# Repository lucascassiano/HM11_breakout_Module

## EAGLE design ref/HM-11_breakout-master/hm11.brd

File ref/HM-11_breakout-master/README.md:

# REFERENCE: 
https://platis.solutions
I'm not the author, I just uploaded here to start making changes on this board file.

# HM-11 BLE module breakout board
Eagle PCB files for a HM-11 Bluetooth Low Energy module, breakout board. Based on the work by [Genoil](https://github.com/Genoil/smartwatch).

Order it directly from [OSH Park](https://oshpark.com/shared_projects/1uC5vV5p) (3.25$ for 3 boards).

Read the story behind it at my [blog](https://platis.solutions/blog/2015/06/11/breakout-board-hm-11-ble/), where you will also find other useful resources such as links to code for a sample Android application.

## Board renders

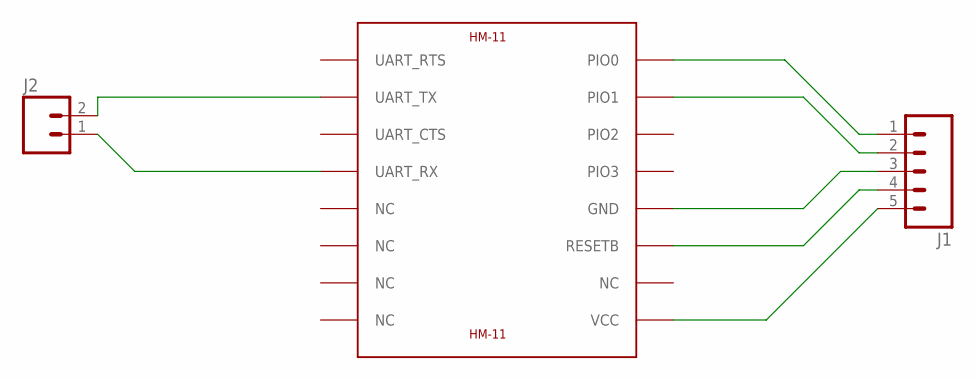
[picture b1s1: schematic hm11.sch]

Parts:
J1: M05PTH_LONGPADS; 1X05_LONGPADS
J2: M02PTH3; 1X02_LONGPADS
U$1: HM-11

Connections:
GND: J1.3, U$1.GND
unnamed: J1.5, U$1.VCC
unnamed: J1.1, U$1.PIO0
unnamed: J2.1, U$1.UART_RX
unnamed: J1.4, U$1.RESETB
unnamed: J1.2, U$1.PIO1
unnamed: J2.2, U$1.UART_TX

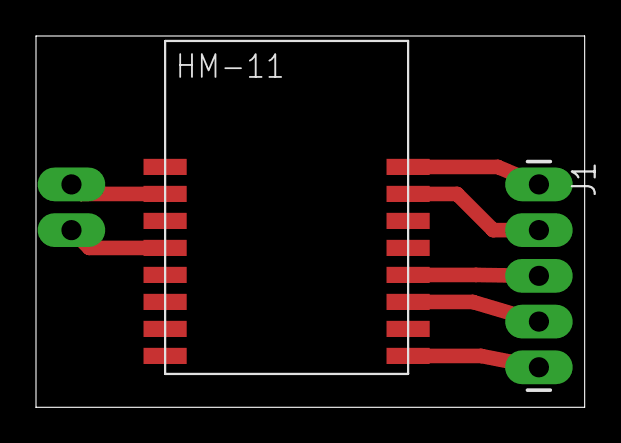
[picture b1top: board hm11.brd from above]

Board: 4 copper layers, 30.5 x 20.6 mm, 3 parts (0 on the bottom side), 7 nets.

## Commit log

2016-11-26 init

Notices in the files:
parts and their libraries:
SparkFun-Connectors: Licensing: Creative Commons ShareAlike 4.0 International - https://creativecommons.org/licenses/by-sa/4.0
